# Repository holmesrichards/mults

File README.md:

# Multiples

This is a buffered multiple module in Kosmo format. It provides two buffered multiple circuits each with one input and four outputs; the input to the second is normalized to the input of the first, so it can function as a 1-in, 8-out multiple.

It is intended to be V/oct-safe. Voltage follower stages are used to guarantee unity gain. Input impedance is 1M instead of the common 100k, resulting in attenuation (of a signal from a source with 1k output impedance) by 0.1% rather than 1% — corresponding to 1.2 cents per octave instead of 12. Output current limiting resistors are in the loop, so there will be no attenuation at the downstream input.

Two things to watch out for:

* There are no stabilization capacitors in the design. With the in-the-loop resistor, the potential exists for op amp instability when driving a capacitive load. In practice this probably means don't use 20 meter long patch cords on the outputs. In more normal usage there is not likely to be a problem.
* Use of JFET op amps (TL074) in voltage followers rather than paired inverting stages means there can be phase reversal if the input signal is less than 4 V from the negative rail, giving incorrect outputs. If your inputs might go more negative than -8 V, use a different multiple. There also is no protection against overvoltage outside the ±12 V range, so exercise care not to connect anything that might give such large voltages.

## Current draw
16 mA +12 V, 16 mA -12 V

## Photos

## Documentation

* [Schematic](Docs/multiples_schematic.pdf)
* PCB layout: [front](Docs/2D/multiples/multiples_front.svg), [back](Docs/2D/multiples/multiples_back.svg)
* [BOM](Docs/BOM/multiples_bom.md)
* [How it works](Docs/howitworks.md)
* [Blog post](https://analogoutputblog.wordpress.com/2023/03/13/buffered-multiples-again/)

## GitHub repository

* [https://github.com/holmesrichards/mults](https://github.com/holmesrichards/mults)

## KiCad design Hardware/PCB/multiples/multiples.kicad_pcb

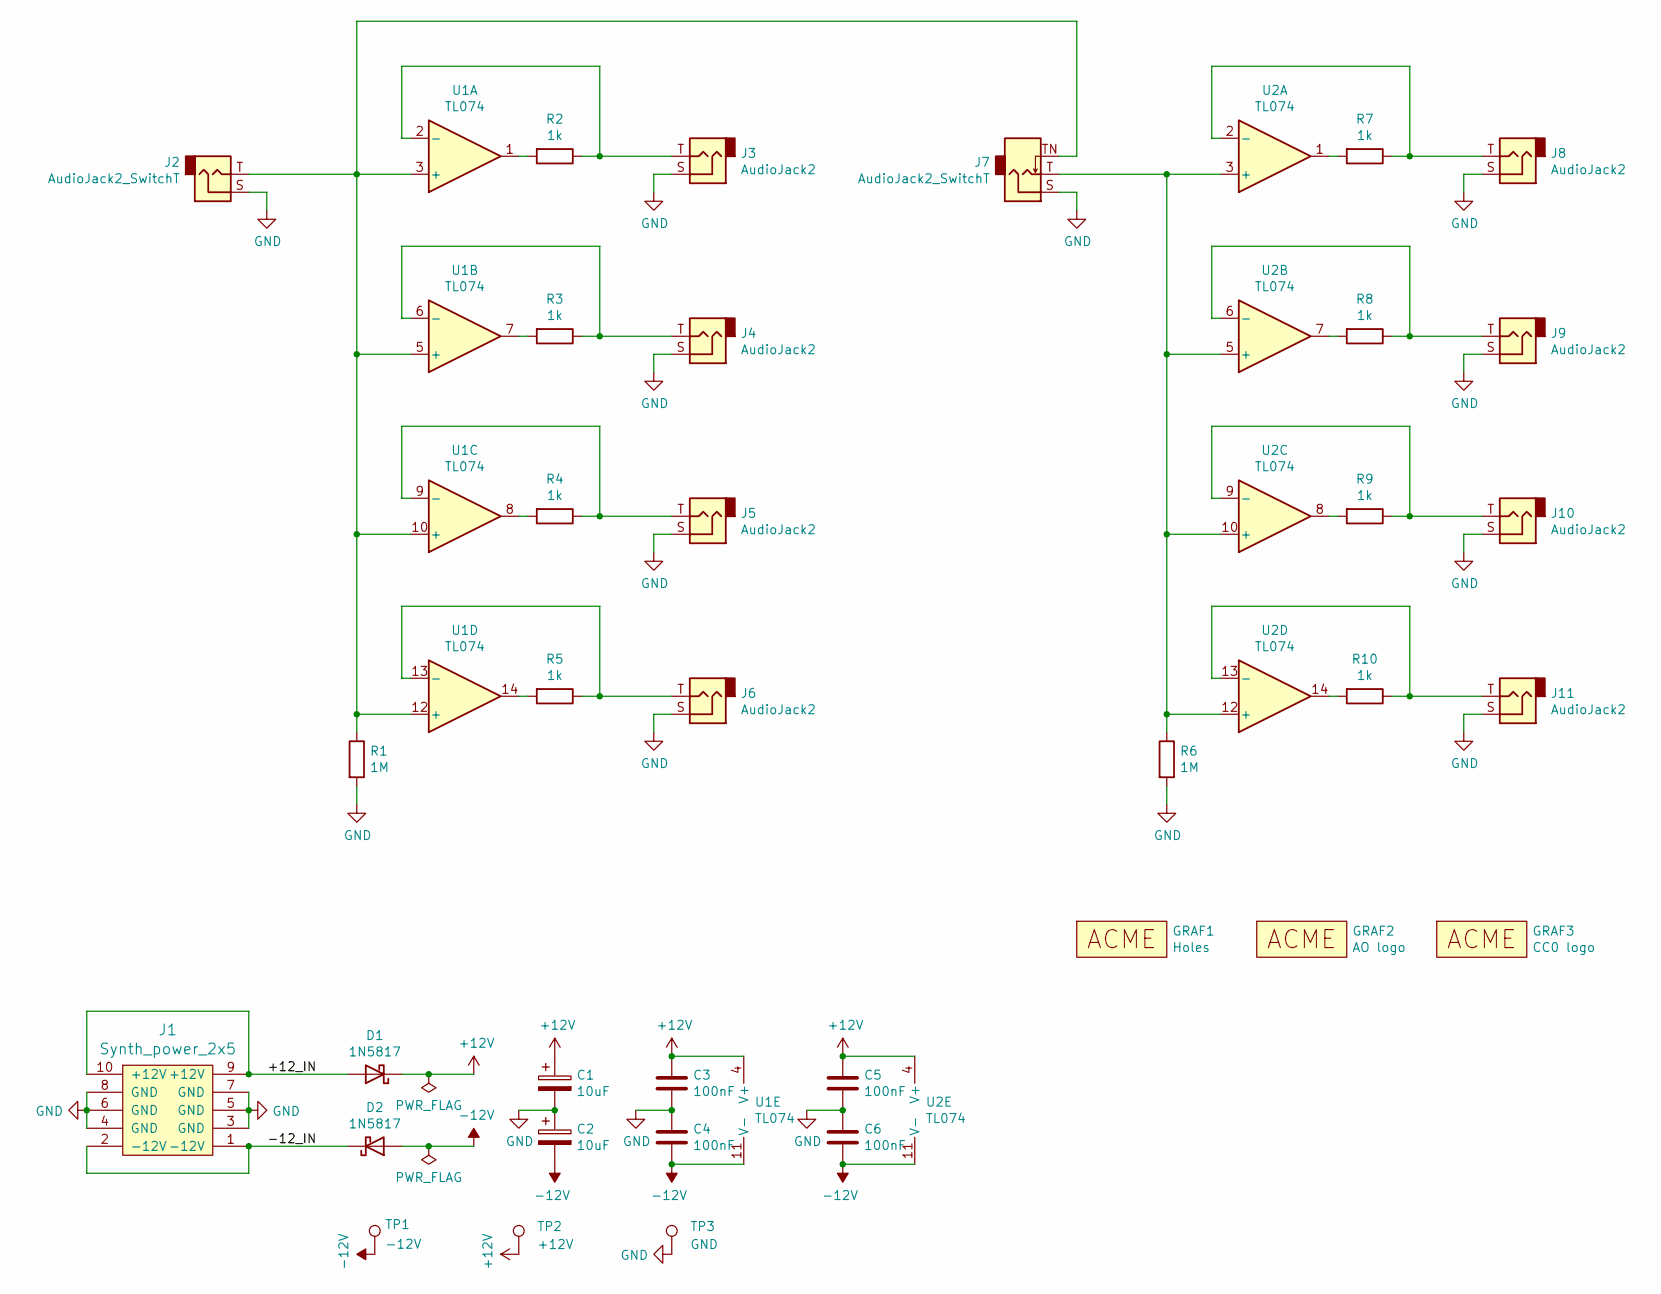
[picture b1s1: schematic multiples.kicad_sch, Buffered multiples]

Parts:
C1, C2: 10uF; CP_Radial_D6.3mm_P2.50mm
C3, C4, C5, C6: 100nF; C_Disc_D3.0mm_W1.6mm_P2.50mm
D1, D2: 1N5817; D_DO-41_SOD81_P10.16mm_Horizontal
GRAF1: Holes; multiples_panel_holes
GRAF2: AO logo; analogoutput
GRAF3: CC0 logo; CC0_logo
J1: Synth_power_2x5; Power_Header
J2, J7: AudioJack2_SwitchT; Jack_6.35mm_PJ_629HAN_slots
J3, J4, J5, J6, J8, J9, J10, J11: AudioJack2; Jack_6.35mm_PJ_629HAN_slots
R1, R6: 1M; R_Axial_DIN0207_L6.3mm_D2.5mm_P10.16mm_Horizontal
R2, R3, R4, R5, R7, R8, R9, R10: 1k; R_Axial_DIN0207_L6.3mm_D2.5mm_P10.16mm_Horizontal
TP1: -12V; TestPoint_THTPad_D1.5mm_Drill0.7mm
TP2: +12V; TestPoint_THTPad_D1.5mm_Drill0.7mm
TP3: GND; TestPoint_THTPad_D1.5mm_Drill0.7mm
U1, U2: TL074; DIP-14_W7.62mm_Socket_LongPads

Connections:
+12V: C1.1, C3.1, C5.1, D1.1 (K), TP2.1, U1.4 (V+), U2.4 (V+)
-12V: C2.2, C4.2, C6.2, D2.2 (A), TP1.1, U1.11 (V-), U2.11 (V-)
/+12_IN: D1.2 (A), J1.9 (+12V), J1.10 (+12V)
/-12_IN: D2.1 (K), J1.1 (-12V), J1.2 (-12V)
GND: C1.2, C2.1, C3.2, C4.1, C5.2, C6.1, J1.3 (GND), J1.4 (GND), J1.5 (GND), J1.6 (GND), J1.7 (GND), J1.8 (GND), J2.S, J3.S, J4.S, J5.S, J6.S, J7.S, J8.S, J9.S, J10.S, J11.S, R1.2, R6.2, TP3.1
unnamed: R2.2, U1.1
unnamed: R3.2, U1.7
unnamed: R4.2, U1.8
unnamed: R5.2, U1.14
unnamed: R7.2, U2.1
unnamed: R8.2, U2.7
unnamed: R9.2, U2.8
unnamed: R10.2, U2.14
unnamed: J2.T, J7.TN, R1.1, U1.3 (+), U1.5 (+), U1.10 (+), U1.12 (+)
unnamed: J3.T, R2.1, U1.2 (-)
unnamed: J4.T, R3.1, U1.6 (-)
unnamed: J5.T, R4.1, U1.9 (-)
unnamed: J6.T, R5.1, U1.13 (-)
unnamed: J7.T, R6.1, U2.3 (+), U2.5 (+), U2.10 (+), U2.12 (+)
unnamed: J8.T, R7.1, U2.2 (-)
unnamed: J9.T, R8.1, U2.6 (-)
unnamed: J10.T, R9.1, U2.9 (-)
unnamed: J11.T, R10.1, U2.13 (-)

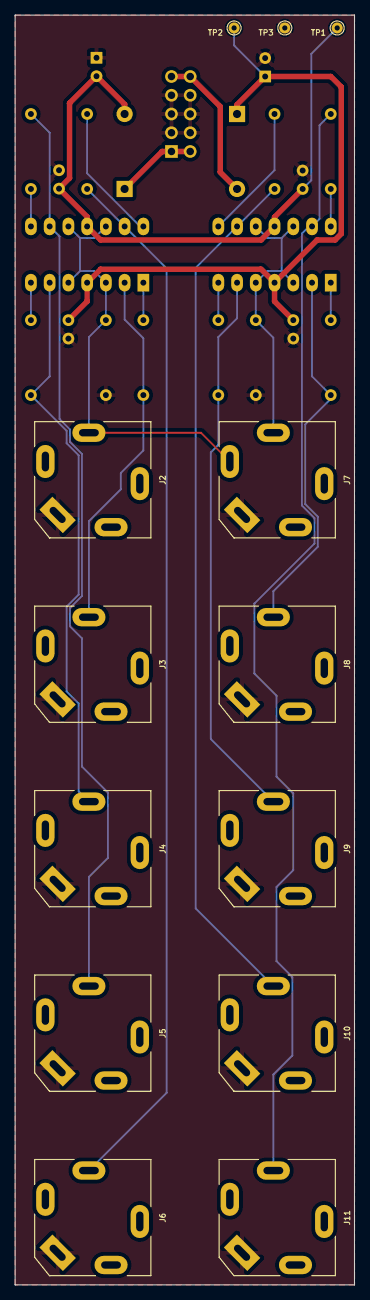
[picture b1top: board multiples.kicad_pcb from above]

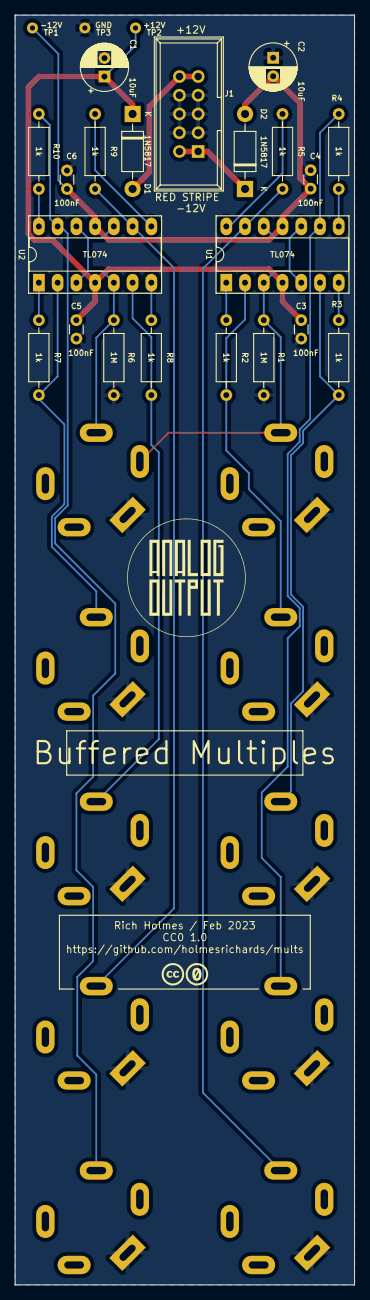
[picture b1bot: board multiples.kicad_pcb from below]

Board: 2 copper layers, 46.0 x 172.1 mm, 37 parts (23 on the bottom side), 23 nets.

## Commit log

2021-05-02 Initial version
2021-07-29 Footprints, ground tip normal
2021-08-07 Kosmo_panel lib update
2021-08-12 svg panel
2021-08-17 PCB layout
2021-08-20 Submodules; panel
2021-08-20 No NPTH specialization
2021-08-21 relocate libraries
2021-08-21 rm project libraries
2021-09-09 Clean up libraries, Schottky footprint update
2021-09-15 SVG decontamination
2021-12-02 Panel art tweak
2022-02-01 Better .gitignore
2022-06-20 Kosmo_panel branch fix
2023-02-05 KiCad 7, libraries to folder
2023-02-06 LICENSE
2023-02-11 Pre fab tweaks
2023-02-11 Pre fab tweaks, Gerbers
2023-02-15 DIP sockets; PDF docs; README
2023-02-21 How it works
2023-02-22 gerbers
2023-02-22 rm libraries
2023-02-22 libraries in new place
2023-03-08 Libraries update
2023-03-08 rm submodules
2023-03-13 reorg
2023-03-13 Docs
2023-03-13 how it works in README
2023-03-15 Add current draw
2023-03-17 mv 2D to Layout
